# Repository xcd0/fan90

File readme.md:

# one hand keyboard fan

片手用キーボードです。G13のような用途を想定しています。  
左手で使うことを想定していますが、右手でも使えるようにPCBは作っています。  
流行りのミニマムなキーボードとは反対方向のマキシマムな方向のキーボードです。  
両手で使うことを想定していませんが、両面対応しているので2つ用意すれば可能です。  

初めての自作キーボードなので楽しみなのと不安なのが混在しています\_(:3 」∠ )\_
あくまで初めてつくる自作キーボードであるため、当然ながら動かない可能性が高いです。

<details>
<summary>開発経緯</summary>

## キーボード割ろうとしたら曲がった
* ありものは素晴らしい、でも自分で作ってみたい。よし、初めてのキーボード自作だ！PCBから作るぞ\\('ω')/
* 今使ってるhelixよい。でもErgodox的な縦のずれがあるキーボードもよさそう。そういうの作ろう...
* 左右分割型のキーボード良い。割りたい！でも左右の通信とかどうやってるんだろう...ちゃんと作れるかな...
* とりあえずキーを並べてみる。小指とか根元に近く配置しよう...
* 見た目汚いな...とりあえずきれいに並べてみるか...あれ、なんか曲がってきた...
* あれこれ片手でフルキーボードいけるんじゃ...

という感じでした\_(:3 」∠ )\_  
つまりキーボードを割ろうとしたが、  
筋力が足りなかったため（左右に分割したときの左右間の通信を電源(VCC,GND)と信号線の3本でどうやって通信してるのかわからなかったので）、  
割れずに曲がってしまった。  
次作るときは割りたい。  
名前は見た目がうちわのようになったため。  もちろん余った基板は重めの団扇として使うことができる。
鍋敷きにしてもよい。
</details>

<details>
<summary>構想</summary>

### コンセプト
以下で東西南北を言うときは、左手で中指の方向を北とした場合の手のひらからの方向を指します。

* 片手でたくさんのキーを使える。
	* フルキーボード相当のキーを使えるものとする。
		* 現状6x15のマトリクスで87キーを配置。
		* 残り３キーはあまり使わない用途向けにリセットスイッチ部品で配置。

* 片手で使いやすい。
	* 指毎の特徴に合わせて配置する。  
		例えば
		* 親指はゲームのコントローラーで多用されるように本来非常に性能が良い。  
		しかしキーボードを使う上で親指を生かすのは難しい。  
		Twitterの投票によると親指に複数のキーを割り当てているときに使っているキーの数はせいぜい4キーらしい。  
		このキーボードでは多めに5キーを割り当てる。
		* 人差し指は性能が良くQWERTYでもほかの指より多いキーを担当する。  
		このキーボードでも人差し指の担当は多くする。
		* 中指は人差し指と同じくらいのせいのがある。中指にも多めのキーを割り当てる。
		* 薬指は中指と一緒に動かないと性能が良くないので、キーボードではあまり性能を発揮できない。
		ただし、北西方向は強く、北西方向に関しては小指より適している。。
		* 小指は短いので、北西方向の移動は難しい。  
		しかし西方向、南西方向はそこそこ性能が良い。
	* 指に合わせてキーを配置する。
		* 変則的な配置なので指１本に対して割り当てられたキーの数は様々。
			* 現状小指20、薬指15、中指12、人差し指31、親指5キー。人差し指と小指は無駄キーを含む。足しても90にはならない。
		* 将来的にはキーを立体的に配置するのもよいが、現状は平面に配置。
	* 指は伸ばした状態のほうが押しやすく、キーを押し分けやすい。
		* 指の根本に近いキーよりも指を伸ばしたときに押すキーのほうが押しやすい。
		* 指の根元に近いキーを減らし、指を伸ばしたときに押すキーを増やす。
	* レイヤーは極力つかわない。
		* シフトキーのように押しながら操作することは片手だと難しい。

* すべてのキーを常に使うキーにはせず、使う用途に合わせてカスタマイズできるよう、無駄にキーを配置する。

### 実現方法

* 以下の2点からキーを扇状に配置する。
	* 小指の性能を発揮できるように小指のキーは手首側に寄せる。
	* 伸ばした状態で使える人差し指、中指のキーを増やす。
* 列方向には揃えず、行方向にはそろえる。
* 無駄にキーを小指の西側、人差し指の東側、すべての指の北側に配置する。つまり一回り大きくする。

### 将来的にやりたいこと

* QMKを使わずに作る。(現状使う)
* C以外の言語で作る。(現状C言語)
* マイコンを複数種類使えるようにする。(現状むずかしい)
* raspberry pi zeroと画面を搭載して、それ単体でPCとして動作させ多機能にする。(現状ソケットのみ用意)
* ケースを3Dプリンターなどでつくる。
* キーを立体的に配置する。

</details>

<details>
<summary>設計</summary>

## PCB設計

kicadを使って設計した。

回路は6x15のマトリクス。column方向からスキャンし、rowを検出する。  
column方向のスキャンは床に転がっていたSN74HC595を使う。  
シフトレジスタを使えば簡単にスキャンできそう。  
これで信号線数を15-5で10本減らせることになる。  
pro microはデジタルIOピンが14本、デジタルとしても使えるアナログIOピンが4本なので、
最大18本をデジタルIOとして使うことができる。
6本をrowのデジタル入力に、5本をシフトレジスタへのデジタル出力に、
2本をリセットスイッチに使用することにした。
配置は特にこだわりなく並べた。このせいで後々苦労するかもしれないがまあ初めてなので良しとする。

## アクリルケース設計

* ケースもとりあえずアクリルで作ることにした。
* ケースもDXFで入稿できるみたいなのでkicadでそのまま作った。
	* SVGでもよさそうだがそもそもSVGで線幅を狭くするとinkscapeやchromeで表示したとき線が描画されない問題があった。
* アクリルは[工房Emerge+](https://www.emergeplus.jp/laser-cutting-service/)を使ってみることにした。
	* elecrowはウェブサイトの調子が良くないのか、そもそもサービス中止中なのか、  
	https://twitter.com/xcd0/status/1233658167684296704  
	のようにfalseとなっていた。
	* 遊舎工房は、キーボードのサイズが大きいので元のアクリル板が最低でもA3より大きな必要があり、  
	A5,A4,450 X 300と、450x300以外の選択肢がなく、このサイズでも2枚発注する必要がある。  
	そして150x300程度の余白ができてしまう。
	* Emarge+は600x300に対応しており、これだと１枚に収まる。なのでここにしてみた。
	* 遊舎工房とEmerge+はillustratorありきの体制で、すごくストレスフルであった。
	* inkscapeは線幅の問題で使えず、外形と内形を色を変えるとかレイヤーを変えるとか言った操作はillustratorがないと難しいというか不可能な作業であった。
	* 今回５個ほどソフトを試したが、どれも満たせずあきらめてillustratorの7日間仕様版を使った。
	* 次回はaiやsvgではなくDXFで入稿したい。
	* elecrow復活してほしい... ← 復活してた
* データ蹴られるかと思ったがとりあえず通った。
* DXFもレイヤー分けていればよいらしい。

</details>

<details>
<summary>作成</summary>

## はんだ付け

[キースイッチを手軽に交換できる Kailh PCBソケット](https://talpkeyboard.stores.jp/items/5e02c5405b120c792616bcf9)
とダイオードをちまちまつけていく。

ダイオードの向きは今のシルクだと上向きになっているが、
本当は下向きが良い。
上向きだと正論理でキースキャンをする形になる。
それでいいと思っていたが、Pro Microは入力端子の内部抵抗がどうもプルアップにしかできないみたい。
今回はもうダイオードをつけてしまったのでPro Microの入力端子に10kΩの抵抗をつけてプルダウンした。
現状のプログラムはプルダウンした回路を前提にしている。
もし誰か同じものを作りたい人がいたら、回路を修正して内蔵プルアップ抵抗を使う負論理のキースキャンにプログラムを変更する方がよい。

ソケットは向きを考えて穴にはめていく。
はめた状態だとフットプリントが完全に隠れてしまうので、はんだを適当につけたら問題ない。
と思いきや、そうでもなくて、フットプリントとソケットが浮いていたりする...
めちゃもりもりはんだを盛った。

フットプリントを少し大きくした方が良いなとわかった。

## 組み立て

構造は簡単なので特に迷うことはないはず。

## プログラム作成

プログラムは適当にさっと作った。
[ここ](https://docs.qmk.fm/#/ja/custom_matrix)を参考にmatrix.cを追加して、matrix.cにシフトレジスタでキースキャンするプログラムを書いた。

上にも書いたが現状正論理で書いているので新しく作るときは負論理にしたほうがよい。

</details>

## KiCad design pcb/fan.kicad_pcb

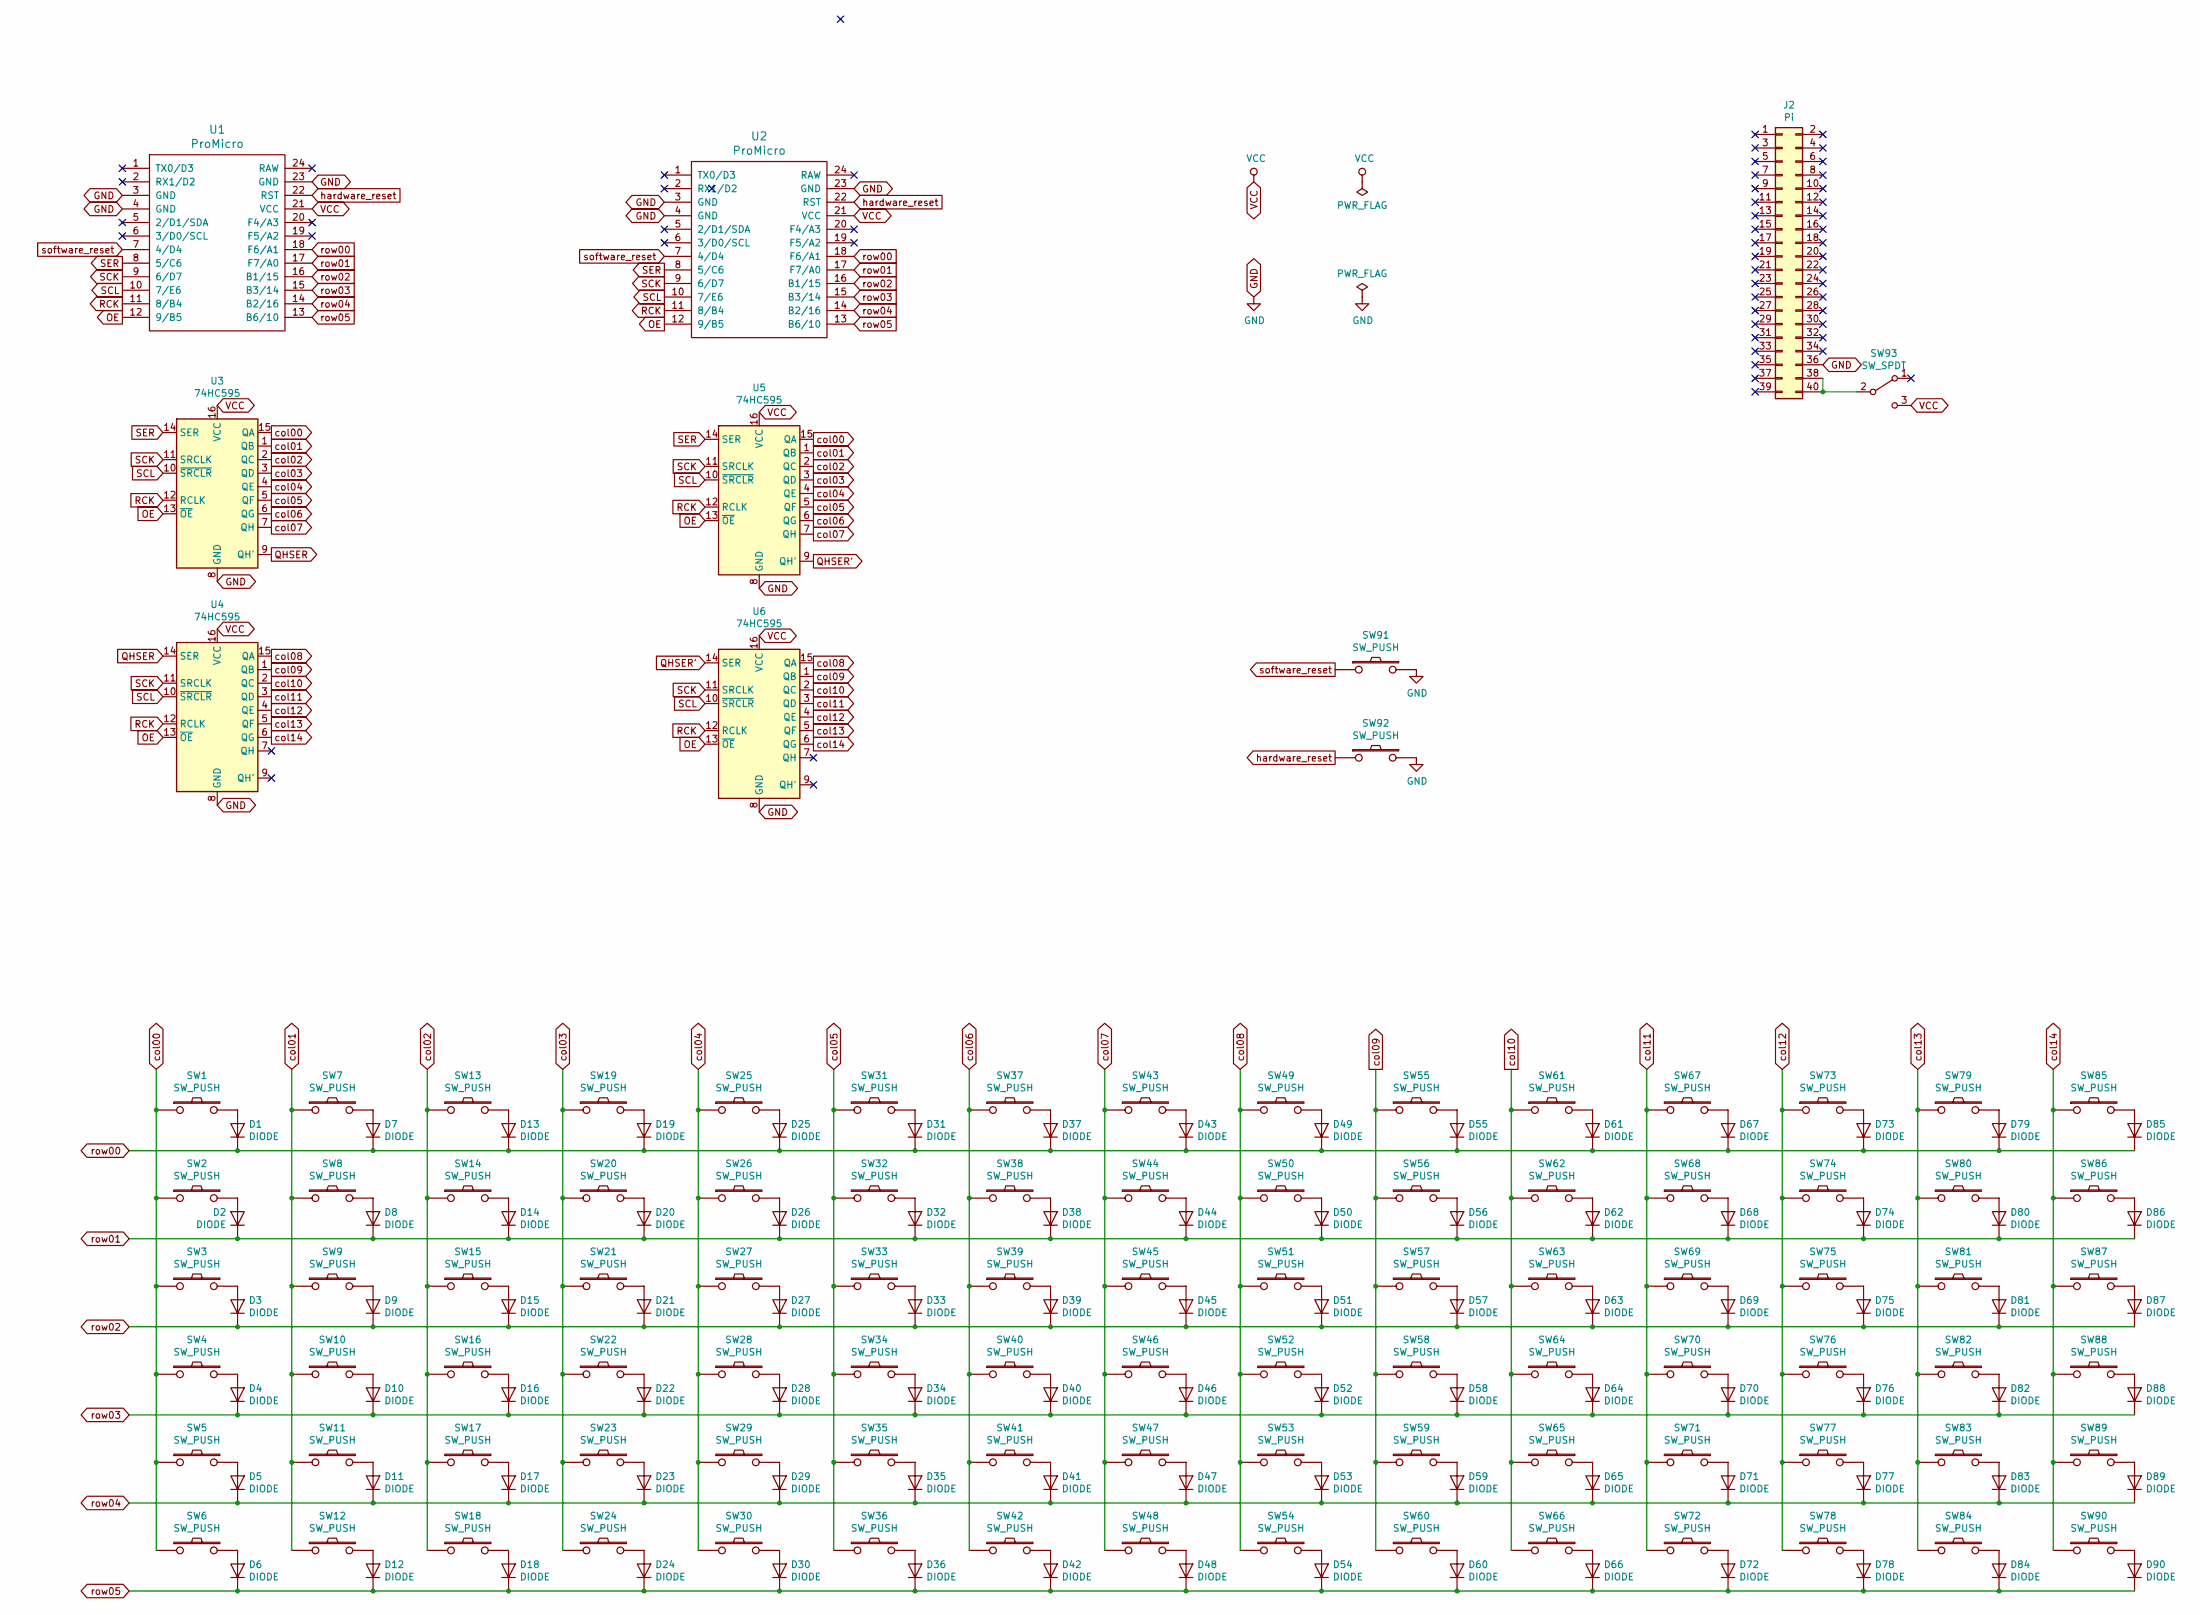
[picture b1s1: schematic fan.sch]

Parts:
D1, D2, D3, D4, D5, D6, D7, D8, D9, D10, D11, D12, D13, D14, D15, D16, D17, D18, D19, D20, D21, D22, D23, D24, D25, D26, D27, D28, D29, D30, D31, D32, D33, D34, D35, D36, D37, D38, D39, D40, D41, D42, D43, D44, D45, D46, D47, D48, D49, D50, D51, D52, D53, D54, D55, D56, D57, D58, D59, D60, D61, D62, D63, D64, D65, D66, D67, D68, D69, D70, D71, D72, D73, D74, D75, D76, D77, D78, D79, D80, D81, D82, D83, D84, D85, D86, D87, D88, D89, D90: DIODE; D3_TH_SMD
J2: Pi; PinSocket_2x20_P2.54mm_Vertical
SW1, SW2, SW3, SW4, SW5, SW6, SW7, SW8, SW9, SW10, SW11, SW12, SW13, SW14, SW15, SW16, SW17, SW18, SW19, SW20, SW21, SW22, SW23, SW24, SW25, SW26, SW27, SW28, SW29, SW30, SW31, SW32, SW33, SW34, SW35, SW36, SW37, SW38, SW39, SW40, SW41, SW42, SW43, SW44, SW45, SW46, SW47, SW48, SW51, SW52, SW53, SW54, SW56, SW57, SW58, SW59, SW60, SW61, SW62, SW63, SW64, SW65, SW66, SW67, SW68, SW69, SW70, SW71, SW72, SW73, SW74, SW75, SW76, SW77, SW78, SW79, SW80, SW81, SW82, SW83, SW84, SW85, SW86, SW87, SW88, SW89, SW90: SW_PUSH; CherryMX_Hotswap
SW49, SW50, SW55, SW91, SW92: SW_PUSH; ResetSW
SW93: SW_SPDT; SW_Slide_1P2T_CK_OS102011MS2Q
U1, U2: ProMicro; ProMicro_v3.6
U3, U4, U5, U6: 74HC595; SN74HC595_DIP-16_W7.62mm_Socket_2

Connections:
GND: J2.36, SW91.2, SW92.2, U1.3 (GND), U1.4 (GND), U1.23 (GND), U2.3 (GND), U2.4 (GND), U2.23 (GND), U3.8 (GND), U4.8 (GND), U5.8 (GND), U6.8 (GND)
unnamed: D1.2 (A), SW1.2
unnamed: D2.2 (A), SW2.2
unnamed: D3.2 (A), SW3.2
unnamed: D4.2 (A), SW4.2
unnamed: D5.2 (A), SW5.2
unnamed: D6.2 (A), SW6.2
unnamed: D7.2 (A), SW7.2
unnamed: D8.2 (A), SW8.2
unnamed: D9.2 (A), SW9.2
unnamed: D10.2 (A), SW10.2
unnamed: D11.2 (A), SW11.2
unnamed: D12.2 (A), SW12.2
unnamed: D13.2 (A), SW13.2
unnamed: D14.2 (A), SW14.2
unnamed: D15.2 (A), SW15.2
unnamed: D16.2 (A), SW16.2
unnamed: D17.2 (A), SW17.2
unnamed: D18.2 (A), SW18.2
unnamed: D19.2 (A), SW19.2
unnamed: D20.2 (A), SW20.2
unnamed: D21.2 (A), SW21.2
unnamed: D22.2 (A), SW22.2
unnamed: D23.2 (A), SW23.2
unnamed: D24.2 (A), SW24.2
unnamed: D25.2 (A), SW25.2
unnamed: D26.2 (A), SW26.2
unnamed: D27.2 (A), SW27.2
unnamed: D28.2 (A), SW28.2
unnamed: D29.2 (A), SW29.2
unnamed: D30.2 (A), SW30.2
unnamed: D31.2 (A), SW31.2
unnamed: D32.2 (A), SW32.2
unnamed: D33.2 (A), SW33.2
unnamed: D34.2 (A), SW34.2
unnamed: D35.2 (A), SW35.2
unnamed: D36.2 (A), SW36.2
unnamed: D37.2 (A), SW37.2
unnamed: D38.2 (A), SW38.2
unnamed: D39.2 (A), SW39.2
unnamed: D40.2 (A), SW40.2
unnamed: D41.2 (A), SW41.2
unnamed: D42.2 (A), SW42.2
unnamed: D43.2 (A), SW43.2
unnamed: D44.2 (A), SW44.2
unnamed: D45.2 (A), SW45.2
unnamed: D46.2 (A), SW46.2
unnamed: D47.2 (A), SW47.2
unnamed: D48.2 (A), SW48.2
unnamed: D49.2 (A), SW49.2
unnamed: D50.2 (A), SW50.2
unnamed: D51.2 (A), SW51.2
unnamed: D52.2 (A), SW52.2
unnamed: D53.2 (A), SW53.2
unnamed: D54.2 (A), SW54.2
unnamed: D55.2 (A), SW55.2
unnamed: D56.2 (A), SW56.2
unnamed: D57.2 (A), SW57.2
unnamed: D58.2 (A), SW58.2
unnamed: D59.2 (A), SW59.2
unnamed: D60.2 (A), SW60.2
unnamed: D61.2 (A), SW61.2
unnamed: D62.2 (A), SW62.2
unnamed: D63.2 (A), SW63.2
unnamed: D64.2 (A), SW64.2
unnamed: D65.2 (A), SW65.2
unnamed: D66.2 (A), SW66.2
unnamed: D67.2 (A), SW67.2
unnamed: D68.2 (A), SW68.2
unnamed: D69.2 (A), SW69.2
unnamed: D70.2 (A), SW70.2
unnamed: D71.2 (A), SW71.2
unnamed: D72.2 (A), SW72.2
unnamed: D73.2 (A), SW73.2
unnamed: D74.2 (A), SW74.2
unnamed: D75.2 (A), SW75.2
unnamed: D76.2 (A), SW76.2
unnamed: D77.2 (A), SW77.2
unnamed: D78.2 (A), SW78.2
unnamed: D79.2 (A), SW79.2
unnamed: D80.2 (A), SW80.2
unnamed: D81.2 (A), SW81.2
unnamed: D82.2 (A), SW82.2
unnamed: D83.2 (A), SW83.2
unnamed: D84.2 (A), SW84.2
unnamed: D85.2 (A), SW85.2
unnamed: D86.2 (A), SW86.2
unnamed: D87.2 (A), SW87.2
unnamed: D88.2 (A), SW88.2
unnamed: D89.2 (A), SW89.2
unnamed: D90.2 (A), SW90.2
unnamed: J2.38, J2.40, SW93.2 (B)
OE: U1.12 (9/B5), U2.12 (9/B5), U3.13 (~OE), U4.13 (~OE), U5.13 (~OE), U6.13 (~OE)
QHSER: U3.9 (QH'), U4.14 (SER)
QHSER': U5.9 (QH'), U6.14 (SER)
RCK: U1.11 (8/B4), U2.11 (8/B4), U3.12 (RCLK), U4.12 (RCLK), U5.12 (RCLK), U6.12 (RCLK)
SCK: U1.9 (6/D7), U2.9 (6/D7), U3.11 (SRCLK), U4.11 (SRCLK), U5.11 (SRCLK), U6.11 (SRCLK)
SCL: U1.10 (7/E6), U2.10 (7/E6), U3.10 (~SRCLR), U4.10 (~SRCLR), U5.10 (~SRCLR), U6.10 (~SRCLR)
SER: U1.8 (5/C6), U2.8 (5/C6), U3.14 (SER), U5.14 (SER)
VCC: SW93.3 (C), U1.21 (VCC), U2.21 (VCC), U3.16 (VCC), U4.16 (VCC), U5.16 (VCC), U6.16 (VCC)
col00: SW1.1, SW2.1, SW3.1, SW4.1, SW5.1, SW6.1, U3.15 (QA), U5.15 (QA)
col01: SW7.1, SW8.1, SW9.1, SW10.1, SW11.1, SW12.1, U3.1 (QB), U5.1 (QB)
col02: SW13.1, SW14.1, SW15.1, SW16.1, SW17.1, SW18.1, U3.2 (QC), U5.2 (QC)
col03: SW19.1, SW20.1, SW21.1, SW22.1, SW23.1, SW24.1, U3.3 (QD), U5.3 (QD)
col04: SW25.1, SW26.1, SW27.1, SW28.1, SW29.1, SW30.1, U3.4 (QE), U5.4 (QE)
col05: SW31.1, SW32.1, SW33.1, SW34.1, SW35.1, SW36.1, U3.5 (QF), U5.5 (QF)
col06: SW37.1, SW38.1, SW39.1, SW40.1, SW41.1, SW42.1, U3.6 (QG), U5.6 (QG)
col07: SW43.1, SW44.1, SW45.1, SW46.1, SW47.1, SW48.1, U3.7 (QH), U5.7 (QH)
col08: SW49.1, SW50.1, SW51.1, SW52.1, SW53.1, SW54.1, U4.15 (QA), U6.15 (QA)
col09: SW55.1, SW56.1, SW57.1, SW58.1, SW59.1, SW60.1, U4.1 (QB), U6.1 (QB)
col10: SW61.1, SW62.1, SW63.1, SW64.1, SW65.1, SW66.1, U4.2 (QC), U6.2 (QC)
col11: SW67.1, SW68.1, SW69.1, SW70.1, SW71.1, SW72.1, U4.3 (QD), U6.3 (QD)
col12: SW73.1, SW74.1, SW75.1, SW76.1, SW77.1, SW78.1, U4.4 (QE), U6.4 (QE)
col13: SW79.1, SW80.1, SW81.1, SW82.1, SW83.1, SW84.1, U4.5 (QF), U6.5 (QF)
col14: SW85.1, SW86.1, SW87.1, SW88.1, SW89.1, SW90.1, U4.6 (QG), U6.6 (QG)
hardware_reset: SW92.1, U1.22 (RST), U2.22 (RST)
row00: D1.1 (K), D7.1 (K), D13.1 (K), D19.1 (K), D25.1 (K), D31.1 (K), D37.1 (K), D43.1 (K), D49.1 (K), D55.1 (K), D61.1 (K), D67.1 (K), D73.1 (K), D79.1 (K), D85.1 (K), U1.18 (F6/A1), U2.18 (F6/A1)
row01: D2.1 (K), D8.1 (K), D14.1 (K), D20.1 (K), D26.1 (K), D32.1 (K), D38.1 (K), D44.1 (K), D50.1 (K), D56.1 (K), D62.1 (K), D68.1 (K), D74.1 (K), D80.1 (K), D86.1 (K), U1.17 (F7/A0), U2.17 (F7/A0)
row02: D3.1 (K), D9.1 (K), D15.1 (K), D21.1 (K), D27.1 (K), D33.1 (K), D39.1 (K), D45.1 (K), D51.1 (K), D57.1 (K), D63.1 (K), D69.1 (K), D75.1 (K), D81.1 (K), D87.1 (K), U1.16 (B1/15), U2.16 (B1/15)
row03: D4.1 (K), D10.1 (K), D16.1 (K), D22.1 (K), D28.1 (K), D34.1 (K), D40.1 (K), D46.1 (K), D52.1 (K), D58.1 (K), D64.1 (K), D70.1 (K), D76.1 (K), D82.1 (K), D88.1 (K), U1.15 (B3/14), U2.15 (B3/14)
row04: D5.1 (K), D11.1 (K), D17.1 (K), D23.1 (K), D29.1 (K), D35.1 (K), D41.1 (K), D47.1 (K), D53.1 (K), D59.1 (K), D65.1 (K), D71.1 (K), D77.1 (K), D83.1 (K), D89.1 (K), U1.14 (B2/16), U2.14 (B2/16)
row05: D6.1 (K), D12.1 (K), D18.1 (K), D24.1 (K), D30.1 (K), D36.1 (K), D42.1 (K), D48.1 (K), D54.1 (K), D60.1 (K), D66.1 (K), D72.1 (K), D78.1 (K), D84.1 (K), D90.1 (K), U1.13 (B6/10), U2.13 (B6/10)
software_reset: SW91.1, U1.7 (4/D4), U2.7 (4/D4)

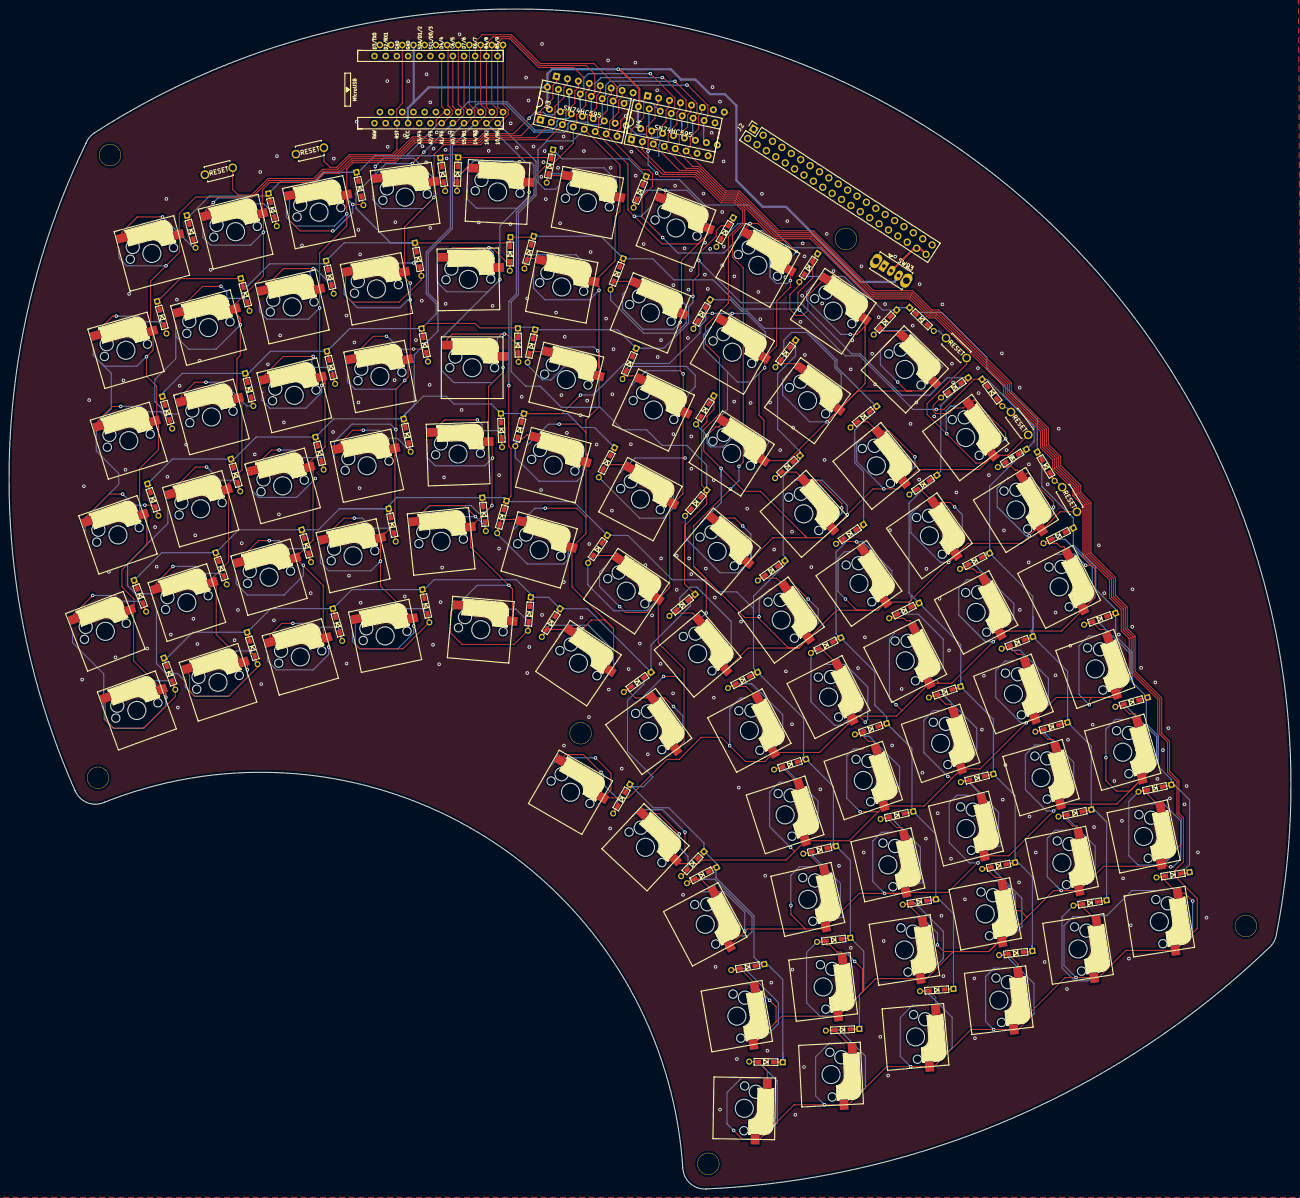
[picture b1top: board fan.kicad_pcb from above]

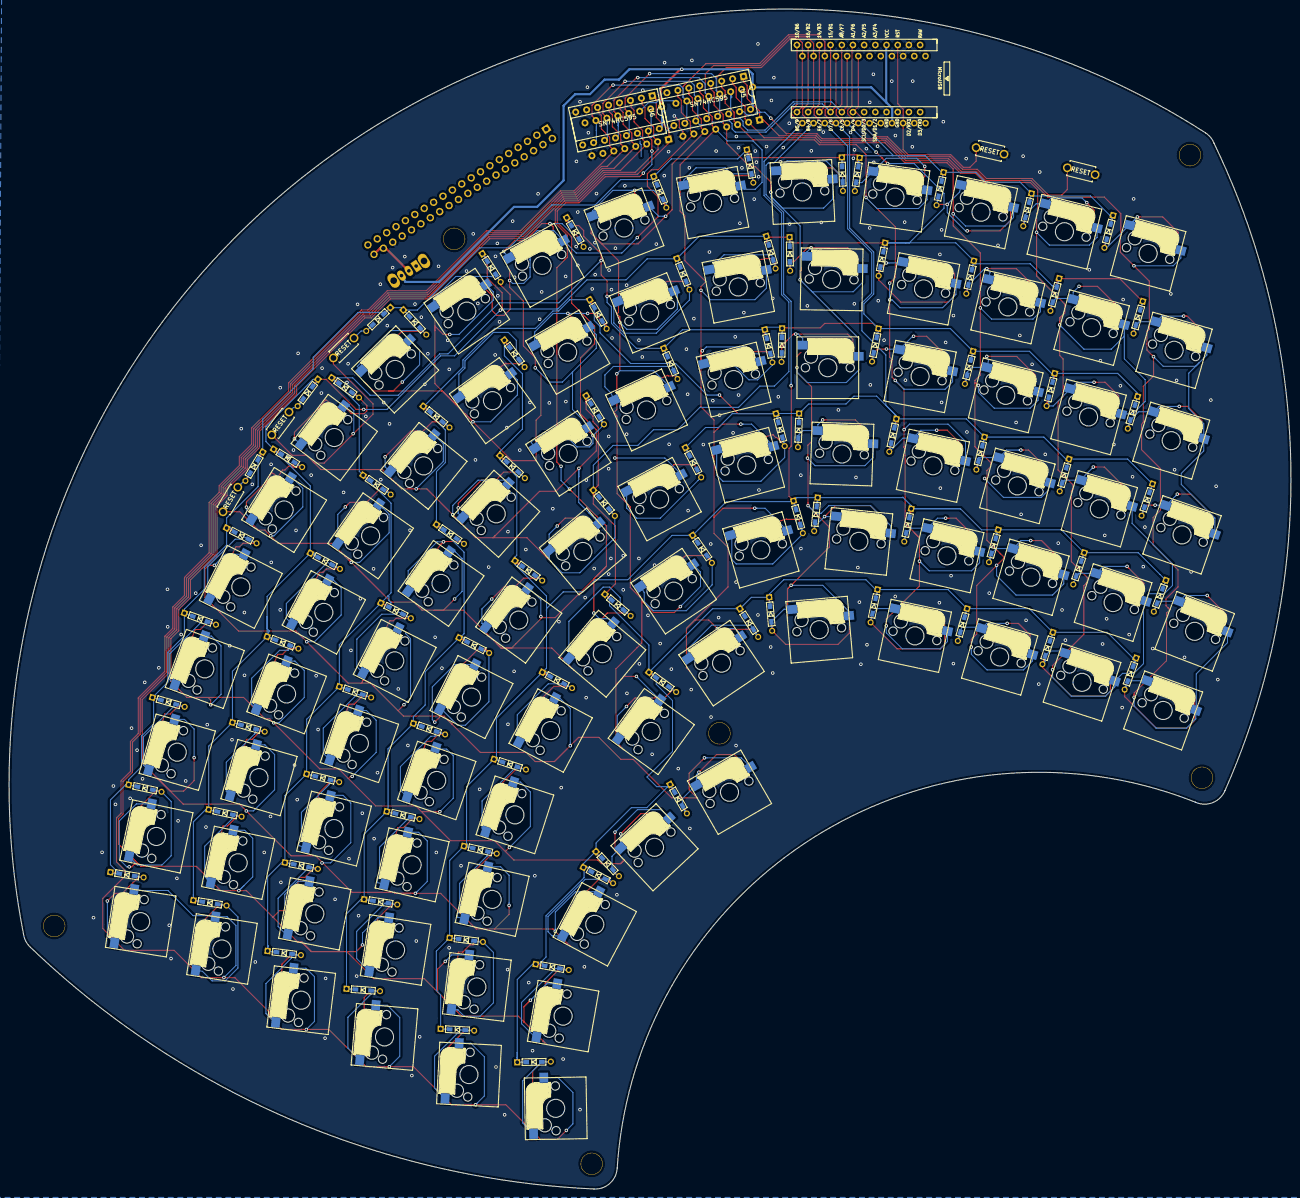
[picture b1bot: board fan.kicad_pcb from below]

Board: 2 copper layers, 290.9 x 267.8 mm, 196 parts (93 on the bottom side), 123 nets.

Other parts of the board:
HOLE1, HOLE2, HOLE3, HOLE4, HOLE5, HOLE6: Val**; HOLE

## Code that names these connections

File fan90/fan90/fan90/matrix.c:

#include "matrix.h"
#include "debounce.h"
#include "wait.h"
#include "print.h"
#include "debug.h"
#include "quantum.h"

/* pro micro pin
  | pin | name    | use            | io  |     | pin | name  | use            | io  |
  | --- | ---     | ---            | --- | --- | --- | ---   | ---            | --- |
  | 1   | TX0/PD3 | -              | -   |     | 24  | VCC   | -              | -   |
  | 2   | RX1/PD2 | -              | -   |     | 23  | GND   | GND            | -   |
  | 3   | GND     | GND            | -   |     | 22  | RESET | hardware reset | i   |
  | 4   | GND     | GND            | -   |     | 21  | VCC   | VCC            | -   |
  | 5   | PD1     | -              | -   |     | 20  | PF4   | -              | -   |
  | 6   | PD0     | -              | -   |     | 19  | PF5   | -              | -   |
  | 7   | PD4     | software reset | i   |     | 18  | PF6   | row00          | i   |
  | 8   | PC6     | SER            | o   |     | 17  | PF7   | row01          | i   |
  | 9   | PD7     | SCK            | o   |     | 16  | PB1   | row02          | i   |
  | 10  | PE6     | SCL            | o   |     | 15  | PB3   | row03          | i   |
  | 11  | PB4     | RCK            | o   |     | 14  | PB2   | row04          | i   |
  | 12  | PB5     | OE             | o   |     | 13  | PB6   | row05          | i   |
*/
// https://docs.qmk.fm/#/custom_matrix
// https://github.com/qmk/qmk_firmware/blob/ece14278efe5168ef20298984bff4b1d5eb43e4b/quantum/matrix_common.c#L108
// https://synapse.kyoto/glossary/74hc595/page001.html


static int row_pins[] = { F6,F7,B1,B3,B2,B6 };
static bool readRowPin(int rowNum ){ return readPin(row_pins[rowNum]); }
static void GPIO_DELAY(void){
	// GPIOでシフトレジスタを制御する際に各信号間で遅延を入れたい場合ここに入れる // delayMicroseconds( 10 ); // <- 使えるか知らない
	_delay_us(10);
}

static void SR_SER_HIGH(void){ writePinHigh(C6); GPIO_DELAY(); }                // C6 SER
static void SR_SER_LOW(void){ writePinLow(C6); GPIO_DELAY(); }                  // C6 SER
static void SR_CLEAR(void){ writePinLow(E6); GPIO_DELAY(); writePinHigh(E6); GPIO_DELAY();}  // E6 CLR
static void SR_CLOCK(void){ writePinLow(D7); GPIO_DELAY(); writePinHigh(D7); GPIO_DELAY();}  // D7 CLK
static void SR_RCLOCK(void){ writePinLow(B4); GPIO_DELAY(); writePinHigh(B4); GPIO_DELAY();} // B4 RCK
//static void SR_OE_OUTPUT_DISABLE(){ writePinHigh(D9); GPIO_DELAY(); }     // D9 OE
//static void SR_OE_OUTPOT_ENABLE(){ writePinLow(D9); GPIO_DELAY(); }     // D9 OE

static void SR_SCAN_COL_SET( int colNum ){
	SR_CLEAR(); // クリア
	uint16_t col = 1;
	col <<= colNum;
	for( uint16_t i = 0; i < MATRIX_COLS; i++ ){
		if( col & 0b1000000000000000 ){
			SR_SER_HIGH();
		} else {
			SR_SER_LOW();
		}
		SR_CLOCK();
	}
	SR_RCLOCK(); // ピンに出力
}

void matrix_init_custom(void) { // {{{
	// TODO: initialize hardware here

	//setPinInputHigh(pin); // Set pin as input with builtin pull-up resistor
	//setPinOutput(pin); // Set pin as output
	//writePinHigh(pin); // Set pin level as high, assuming it is an output
	//writePinLow(pin); // Set pin level as low, assuming it is an output
	//readPin(pin); // Returns the level of the pin

	// シフトレジスタの設定
	// ピンの入出力設定
	setPinInputHigh(D4);
	setPinInputHigh(F6);
	setPinInputHigh(F7);
	setPinInputHigh(B1);
	setPinInputHigh(B3);
	setPinInputHigh(B2);
	setPinInputHigh(B6);
	setPinOutput(C6);
	setPinOutput(D7);
	setPinOutput(E6);
	setPinOutput(B4);
	setPinOutput(B5);
	SR_CLEAR();
	SR_RCLOCK();
} // }}}

bool matrix_scan_custom(matrix_row_t current_matrix[]) {
	bool matrix_has_changed = false;
	// TODO: add matrix scanning routine here

	for (uint16_t c = 0; c < MATRIX_COLS; c++) {
		SR_SCAN_COL_SET(c); // シフトレジスタでc列だけHIGHにする
		for( uint8_t r = 0; r < MATRIX_ROWS; r++ ){
			matrix_row_t last_row_value = current_matrix[r];
			current_matrix[c] = readRowPin(r) ? 0 : (MATRIX_ROW_SHIFTER << c);
			matrix_has_changed |= (last_row_value != current_matrix[c]);
		}
	}

	return matrix_has_changed;
}

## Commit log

2020-03-16 fan90を切り分けた
2020-03-16 fan90専用のリポジトリにした
2020-03-18 add program
2020-03-19 matrix.c 少し書いた
2020-03-20 うごかない
2020-03-20 commit できてなかった_(:3 」∠ )_
2020-03-20 シンボリックリンクを張るbatファイルを追加
2020-03-21 いきづまった
2020-03-21 じわっと進んだ
2020-03-21 うごいた
2020-03-21 とりあえずいったん完成とする。 キーマップはじっくり考える
2020-03-22 update keymap
